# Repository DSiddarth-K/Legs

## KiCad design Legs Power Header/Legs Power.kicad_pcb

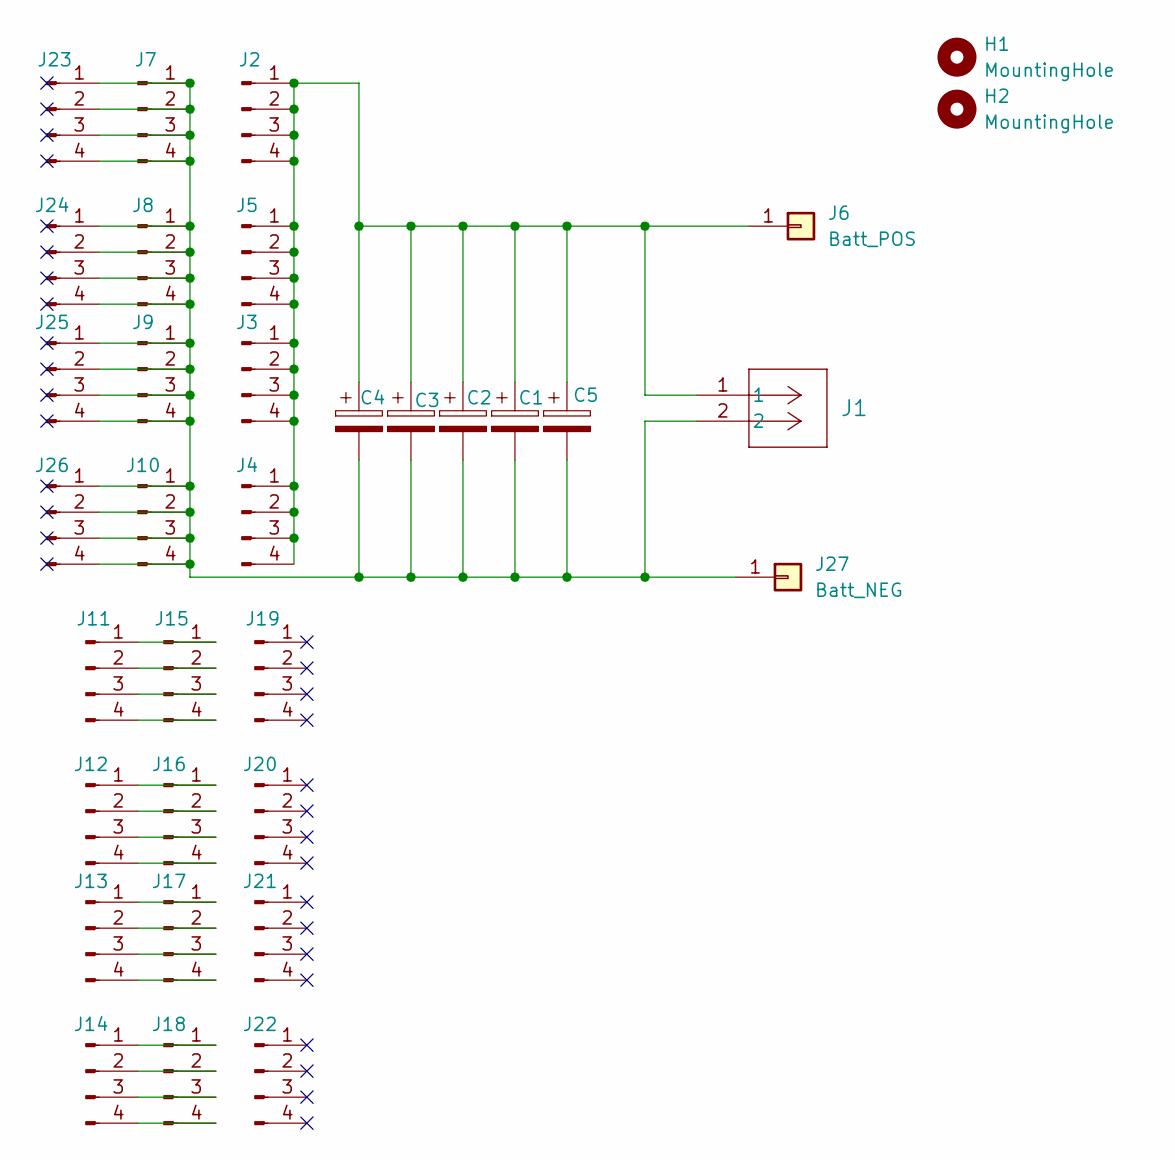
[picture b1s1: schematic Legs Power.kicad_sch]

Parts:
C1, C2, C3, C4, C5: C_Polarized; CP_Radial_D12.5mm_P5.00mm
H1, H2: MountingHole; MountingHole_3.2mm_M3
J1: CONN_1935776_PXC
J2, J3, J4, J5, J7, J8, J9, J10, J11, J12, J13, J14, J15, J16, J17, J18, J19, J20, J21, J22, J23, J24, J25, J26: Conn_01x04_Pin; PinHeader_1x04_P2.54mm_Vertical
J6: Batt_POS; SolderWirePad_1x01_SMD_5x10mm
J27: Batt_NEG; SolderWirePad_1x01_SMD_5x10mm

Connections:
unnamed 0: C1.1, C2.1, C3.1, C4.1, C5.1, J1.1, J2.1, J2.2, J2.3, J2.4, J3.1, J3.2, J3.3, J3.4, J4.1, J4.2, J4.3, J4.4, J5.1, J5.2, J5.3, J5.4, J6.1; also elsewhere on the board
unnamed 1: C1.2, C2.2, C3.2, C4.2, C5.2, J1.2, J7.1, J7.2, J7.3, J7.4, J8.1, J8.2, J8.3, J8.4, J9.1, J9.2, J9.3, J9.4, J10.1, J10.2, J10.3, J10.4, J23.1, J23.2, J23.3, J23.4, J24.1, J24.2, J24.3, J24.4, J25.1, J25.2, J25.3, J25.4, J26.1, J26.2, J26.3, J26.4, J27.1; also elsewhere on the board
unnamed: J11.1, J15.1
unnamed: J11.2, J15.2
unnamed: J11.3, J15.3
unnamed: J11.4, J15.4
unnamed: J12.1, J16.1
unnamed: J12.2, J16.2
unnamed: J12.3, J16.3
unnamed: J12.4, J16.4
unnamed: J13.1, J17.1
unnamed: J13.2, J17.2
unnamed: J13.3, J17.3
unnamed: J13.4, J17.4
unnamed: J14.1, J18.1
unnamed: J14.2, J18.2
unnamed: J14.3, J18.3
unnamed: J14.4, J18.4

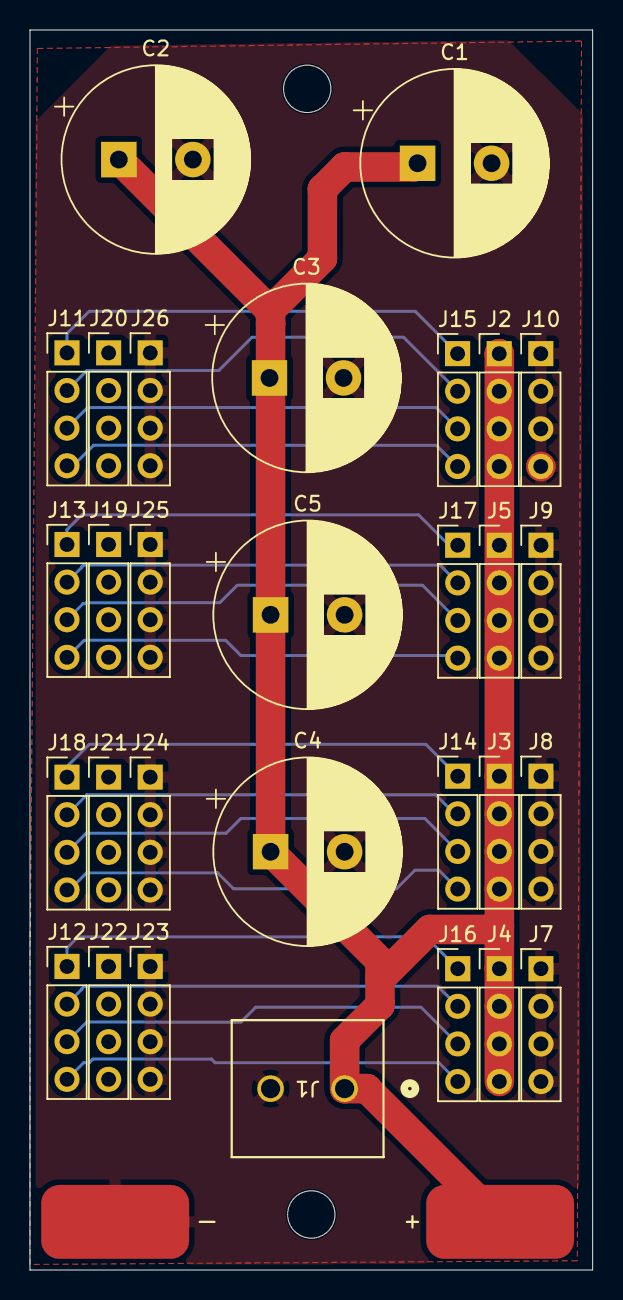
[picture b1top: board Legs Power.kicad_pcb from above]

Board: 2 copper layers, 38.0 x 83.8 mm, 34 parts (0 on the bottom side), 18 nets.

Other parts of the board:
+: Batt_POS; SolderWirePad_1x01_SMD_5x10mm
I: I; SolderWirePad_1x01_SMD_5x10mm

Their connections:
unnamed 0: +.1 (Pin_1_1); also elsewhere on the board
unnamed 1: I.1 (Pin_1_1); also elsewhere on the board
